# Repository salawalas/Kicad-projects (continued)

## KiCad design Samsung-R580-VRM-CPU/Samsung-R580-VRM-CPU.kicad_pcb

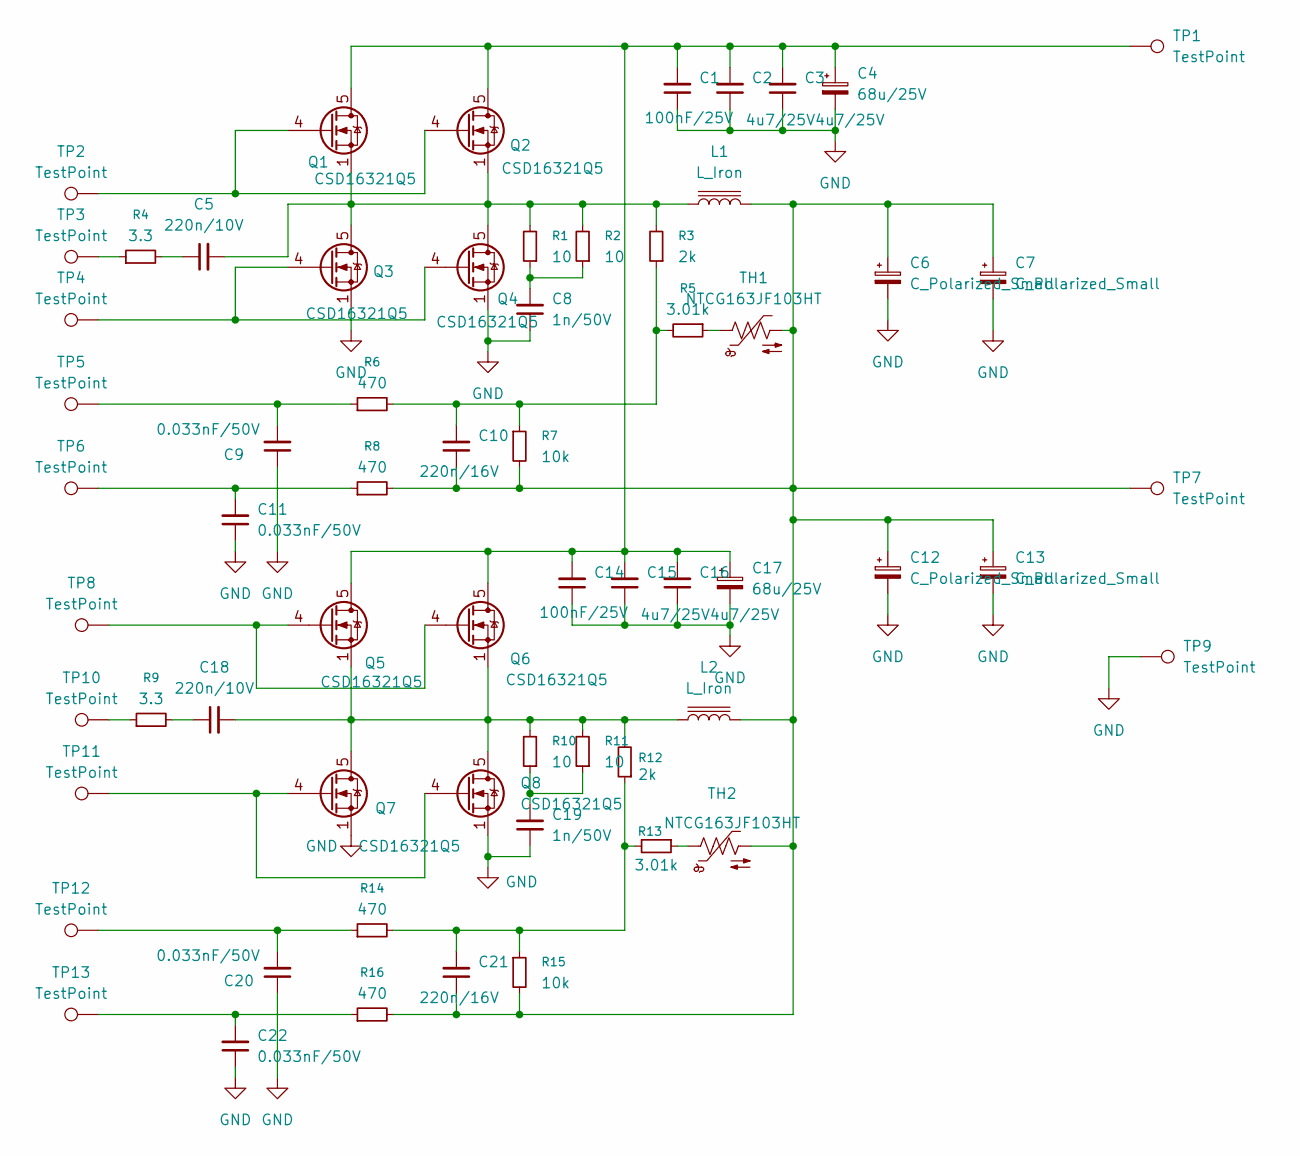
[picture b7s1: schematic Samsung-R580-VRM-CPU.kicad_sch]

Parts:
C1, C14: 100nF/25V; C_0805_2012Metric
C2, C3, C15, C16: 4u7/25V; C_0805_2012Metric
C4, C17: 68u/25V; CP_Elec_5x5.8
C5, C18: 220n/10V; C_0805_2012Metric
C6, C7, C12, C13: C_Polarized_Small; CP_EIA-3528-21_Kemet-B_HandSolder
C8, C19: 1n/50V; C_0805_2012Metric
C9, C11, C20, C22: 0.033nF/50V; C_0805_2012Metric
C10, C21: 220n/16V; C_0805_2012Metric
L1, L2: L_Iron; L_12x12mm_H6mm
Q1, Q2, Q3, Q4, Q5, Q6, Q7, Q8: CSD16321Q5; TDSON-8-1
R1, R2, R10, R11: 10; R_0805_2012Metric
R3, R12: 2k; R_0805_2012Metric
R4, R9: 3.3; R_0805_2012Metric
R5, R13: 3.01k; R_0805_2012Metric
R6, R8, R14, R16: 470; R_0805_2012Metric
R7, R15: 10k; R_0805_2012Metric
TH1, TH2: NTCG163JF103HT; R_0603_1608Metric
TP1, TP2, TP3, TP4, TP5, TP6, TP7, TP8, TP9, TP10, TP11, TP12, TP13: TestPoint; TestPoint_THTPad_1.0x1.0mm_Drill0.5mm

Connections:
GND: C1.1, C2.1, C3.1, C4.2, C6.2, C7.2, C8.1, C9.1, C11.1, C12.2, C13.2, C14.1, C15.1, C16.1, C17.2, C19.1, C20.1, C22.1, Q3.1 (S), Q3.2 (S), Q3.3 (S), Q4.1 (S), Q4.2 (S), Q4.3 (S), Q7.1 (S), Q7.2 (S), Q7.3 (S), Q8.1 (S), Q8.2 (S), Q8.3 (S), TP9.1
unnamed: C5.1, R4.2
unnamed: C8.2, R1.1, R2.1
unnamed: C9.2, R6.1, TP5.1
unnamed: C6.1, C7.1, C10.1, C12.1, C13.1, C21.1, L1.2, L2.2, R7.2, R8.2, R15.2, R16.2, TH1.2, TH2.2, TP7.1
unnamed: C10.2, R3.1, R5.2, R6.2, R7.1
unnamed: C11.2, R8.1, TP6.1
unnamed: C18.1, R9.2
unnamed: C19.2, R10.1, R11.1
unnamed: C20.2, R14.1, TP12.1
unnamed: C21.2, R12.1, R13.2, R14.2, R15.1
unnamed: C22.2, R16.1, TP13.1
unnamed: C1.2, C2.2, C3.2, C4.1, C14.2, C15.2, C16.2, C17.1, Q1.5 (D), Q2.5 (D), Q5.5 (D), Q6.5 (D), TP1.1
unnamed: Q1.4 (G), Q2.4 (G), TP2.1
unnamed: C5.2, L1.1, Q1.1 (S), Q1.2 (S), Q1.3 (S), Q2.1 (S), Q2.2 (S), Q2.3 (S), Q3.5 (D), Q4.5 (D), R1.2, R2.2, R3.2
unnamed: Q3.4 (G), Q4.4 (G), TP4.1
unnamed: Q5.4 (G), Q6.4 (G), TP8.1
unnamed: C18.2, L2.1, Q5.1 (S), Q5.2 (S), Q5.3 (S), Q6.1 (S), Q6.2 (S), Q6.3 (S), Q7.5 (D), Q8.5 (D), R10.2, R11.2, R12.2
unnamed: Q7.4 (G), Q8.4 (G), TP11.1
unnamed: R4.1, TP3.1
unnamed: R5.1, TH1.1
unnamed: R9.1, TP10.1
unnamed: R13.1, TH2.1

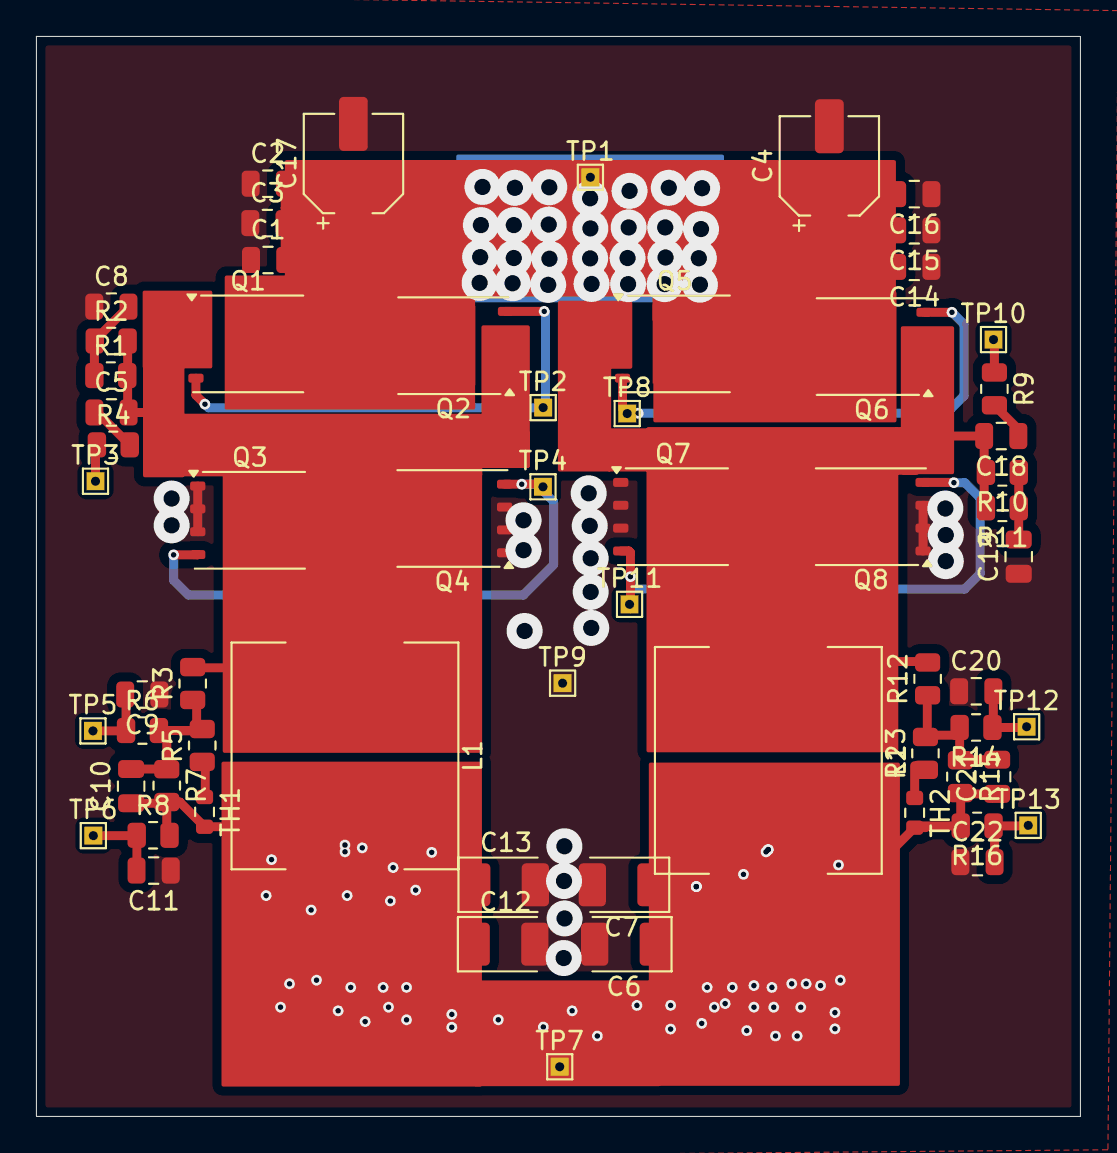
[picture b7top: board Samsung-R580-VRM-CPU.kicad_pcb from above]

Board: 6 copper layers, 58.0 x 60.0 mm, 63 parts (0 on the bottom side), 23 nets.

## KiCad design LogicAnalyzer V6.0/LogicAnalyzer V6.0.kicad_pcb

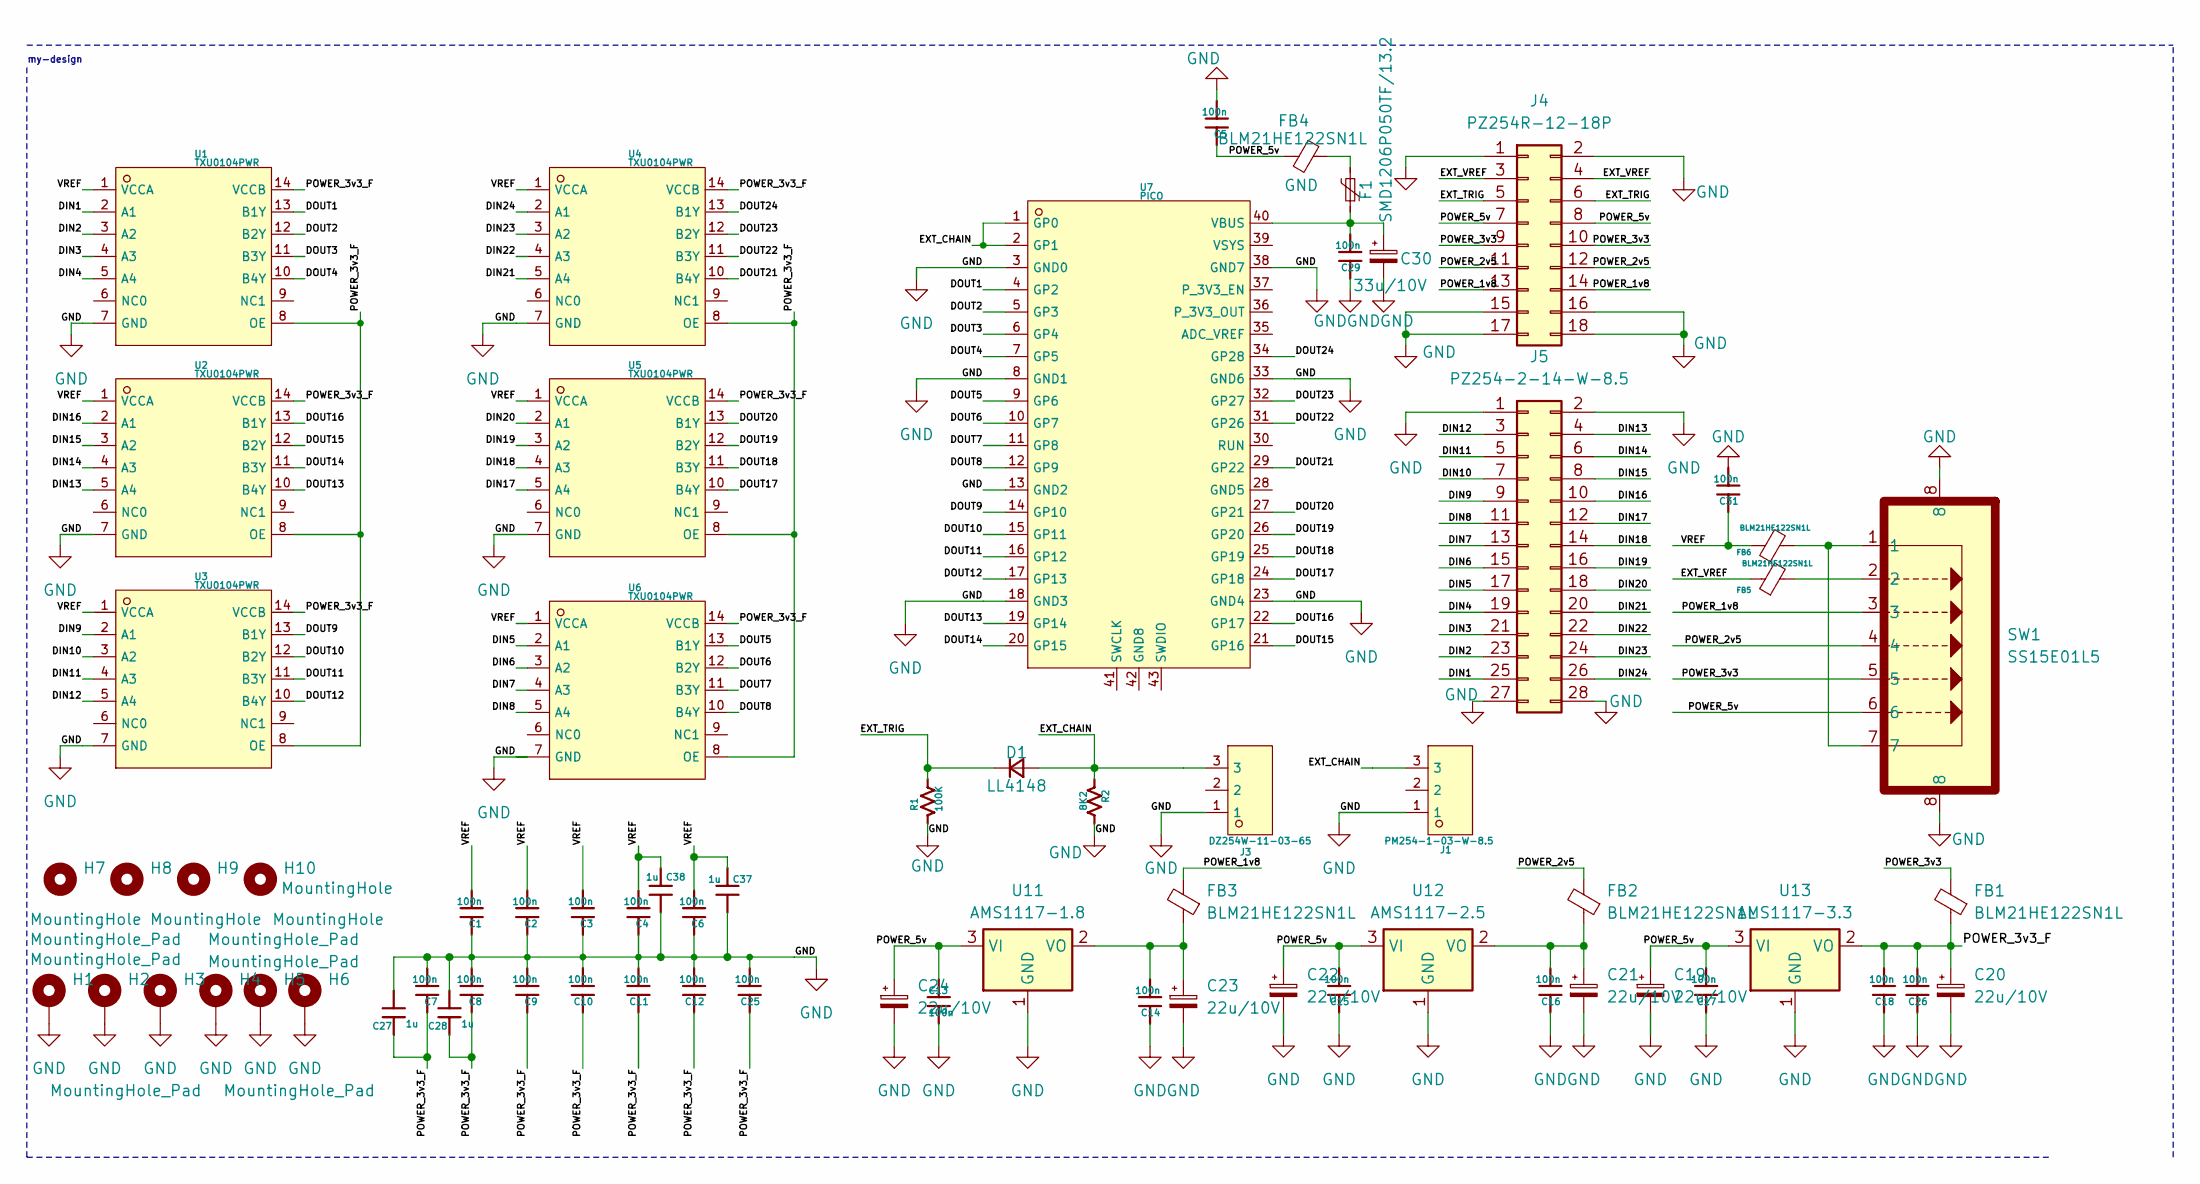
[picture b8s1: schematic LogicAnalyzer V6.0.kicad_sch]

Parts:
C1, C2, C3, C4, C5, C6, C7, C8, C9, C10, C11, C12, C13, C14, C15, C16, C17, C18, C25, C26, C29, C31: 100n; C_0805_2012Metric; MPN 0402X104M160CT
C19, C20, C21, C22, C23, C24: 22u/10V; CP_Radial_Tantal_D4.5mm_P2.50mm
C27, C28, C37, C38: 1u; C_0805_2012Metric; MPN 0402X104M160CT
C30: 33u/10V; CP_Radial_Tantal_D4.5mm_P2.50mm
D1: LL4148; D_MiniMELF
F1: SMD1206P050TF/13.2; Fuse_1206_3216Metric_Pad1.42x1.75mm_HandSolder
FB1, FB2, FB3, FB4, FB5, FB6: BLM21HE122SN1L; L_0805_2012Metric
H1, H2, H3, H4, H5, H6: MountingHole_Pad; MountingHole_2.5mm_Pad_Via
H7, H8, H9, H10: MountingHole; MountingHole_2.2mm_M2
J1: PM254-1-03-W-8.5; PinHeader_1x03_P2.54mm_Horizontal; MPN PM254-1-03-W-8.5
J3: DZ254W-11-03-65; PinHeader_1x03_P2.54mm_Horizontal; MPN DZ254W-11-03-65
J4: PZ254R-12-18P; PinHeader_2x09_P2.54mm_Horizontal
J5: PZ254-2-14-W-8.5; PinHeader_2x14_P2.54mm_Horizontal
R1: 100K; R_0805_2012Metric; MPN CRCW0402100KFKEE
R2: 8K2; R_0805_2012Metric; MPN CR0402AJW-822GLF
SW1: SS15E01L5; XKB Connection SS15E01L5
U1: TXU0104PWR; TSSOP_14_L5_0_W4_4_P0_65_LS6_4_BL_5; MPN TXU0104PWR
U2: TXU0104PWR; TSSOP_14_L5_0_W4_4_P0_65_LS6_4_BL_4; MPN TXU0104PWR
U3: TXU0104PWR; TSSOP_14_L5_0_W4_4_P0_65_LS6_4_BL; MPN TXU0104PWR
U4: TXU0104PWR; TSSOP_14_L5_0_W4_4_P0_65_LS6_4_BL_3; MPN TXU0104PWR
U5: TXU0104PWR; TSSOP_14_L5_0_W4_4_P0_65_LS6_4_BL_1; MPN TXU0104PWR
U6: TXU0104PWR; TSSOP_14_L5_0_W4_4_P0_65_LS6_4_BL_2; MPN TXU0104PWR
U7: PICO; COMM_SMD_L51_0_W21_0_P2_54_SC0916; MPN PICO
U11: AMS1117-1.8; SOT-223-3_TabPin2
U12: AMS1117-2.5; SOT-223-3_TabPin2
U13: AMS1117-3.3; SOT-223-3_TabPin2

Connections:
/DIN1: J5.25, U1.2 (A1)
/DIN2: J5.23, U1.3 (A2)
/DIN3: J5.21, U1.4 (A3)
/DIN4: J5.19, U1.5 (A4)
/DIN5: J5.17, U6.2 (A1)
/DIN6: J5.15, U6.3 (A2)
/DIN7: J5.13, U6.4 (A3)
/DIN8: J5.11, U6.5 (A4)
/DIN9: J5.9, U3.2 (A1)
/DIN10: J5.7, U3.3 (A2)
/DIN11: J5.5, U3.4 (A3)
/DIN12: J5.3, U3.5 (A4)
/DIN13: J5.4, U2.5 (A4)
/DIN14: J5.6, U2.4 (A3)
/DIN15: J5.8, U2.3 (A2)
/DIN16: J5.10, U2.2 (A1)
/DIN17: J5.12, U5.5 (A4)
/DIN18: J5.14, U5.4 (A3)
/DIN19: J5.16, U5.3 (A2)
/DIN20: J5.18, U5.2 (A1)
/DIN21: J5.20, U4.5 (A4)
/DIN22: J5.22, U4.4 (A3)
/DIN23: J5.24, U4.3 (A2)
/DIN24: J5.26, U4.2 (A1)
/DOUT1: U1.13 (B1Y), U7.4 (GP2)
/DOUT2: U1.12 (B2Y), U7.5 (GP3)
/DOUT3: U1.11 (B3Y), U7.6 (GP4)
/DOUT4: U1.10 (B4Y), U7.7 (GP5)
/DOUT5: U6.13 (B1Y), U7.9 (GP6)
/DOUT6: U6.12 (B2Y), U7.10 (GP7)
/DOUT7: U6.11 (B3Y), U7.11 (GP8)
/DOUT8: U6.10 (B4Y), U7.12 (GP9)
/DOUT9: U3.13 (B1Y), U7.14 (GP10)
/DOUT10: U3.12 (B2Y), U7.15 (GP11)
/DOUT11: U3.11 (B3Y), U7.16 (GP12)
/DOUT12: U3.10 (B4Y), U7.17 (GP13)
/DOUT13: U2.10 (B4Y), U7.19 (GP14)
/DOUT14: U2.11 (B3Y), U7.20 (GP15)
/DOUT15: U2.12 (B2Y), U7.21 (GP16)
/DOUT16: U2.13 (B1Y), U7.22 (GP17)
/DOUT17: U5.10 (B4Y), U7.24 (GP18)
/DOUT18: U5.11 (B3Y), U7.25 (GP19)
/DOUT19: U5.12 (B2Y), U7.26 (GP20)
/DOUT20: U5.13 (B1Y), U7.27 (GP21)
/DOUT21: U4.10 (B4Y), U7.29 (GP22)
/DOUT22: U4.11 (B3Y), U7.31 (GP26)
/DOUT23: U4.12 (B2Y), U7.32 (GP27)
/DOUT24: U4.13 (B1Y), U7.34 (GP28)
/EXT_CHAIN: D1.2 (A), J1.3, J3.3, R2.1, U7.1 (GP0), U7.2 (GP1)
/EXT_TRIG: D1.1 (K), J4.5, J4.6, R1.2
/EXT_VREF: FB5.1, J4.3, J4.4
/POWER_1v8: FB3.2, J4.13, J4.14, SW1.3
/POWER_2v5: FB2.2, J4.11, J4.12, SW1.4
/POWER_3v3: FB1.2, J4.9, J4.10, SW1.5
/POWER_3v3_F: C7.1, C8.1, C9.1, C10.1, C11.1, C12.1, C18.2, C20.1, C25.1, C26.2, C27.2, C28.2, FB1.1, U1.8 (OE), U1.14 (VCCB), U2.8 (OE), U2.14 (VCCB), U3.8 (OE), U3.14 (VCCB), U4.8 (OE), U4.14 (VCCB), U5.8 (OE), U5.14 (VCCB), U6.8 (OE), U6.14 (VCCB), U13.2 (VO)
/POWER_5v: C5.1, C13.1, C15.2, C17.2, C19.1, C22.1, C24.1, FB4.2, J4.7, J4.8, SW1.6, U11.3 (VI), U12.3 (VI), U13.3 (VI)
/VREF: C1.2, C2.2, C3.2, C4.2, C6.2, C31.1, C37.1, C38.1, FB6.1, U1.1 (VCCA), U2.1 (VCCA), U3.1 (VCCA), U4.1 (VCCA), U5.1 (VCCA), U6.1 (VCCA)
GND: C1.1, C2.1, C3.1, C4.1, C5.2, C6.1, C7.2, C8.2, C9.2, C10.2, C11.2, C12.2, C13.2, C14.1, C15.1, C16.1, C17.1, C18.1, C19.2, C20.2, C21.2, C22.2, C23.2, C24.2, C25.2, C26.1, C27.1, C28.1, C29.1, C30.2, C31.2, C37.2, C38.2, H1.1, H2.1, H3.1, H4.1, H5.1, H6.1, J1.1, J3.1, J4.1, J4.2, J4.15, J4.16, J4.17, J4.18, J5.1, J5.2, J5.27, J5.28, R1.1, R2.2, SW1.8, U1.7 (GND), U2.7 (GND), U3.7 (GND), U4.7 (GND), U5.7 (GND), U6.7 (GND), U7.3 (GND0), U7.8 (GND1), U7.13 (GND2), U7.18 (GND3), U7.23 (GND4), U7.33 (GND6), U7.38 (GND7), U11.1 (GND), U12.1 (GND), U13.1 (GND)
unnamed: F1.2, FB4.1
unnamed: FB5.2, SW1.2
unnamed: FB6.2, SW1.1, SW1.7
unnamed: C29.2, C30.1, F1.1, U7.40 (VBUS)
unnamed: C14.2, C23.1, FB3.1, U11.2 (VO)
unnamed: C16.2, C21.1, FB2.1, U12.2 (VO)

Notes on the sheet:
my-design

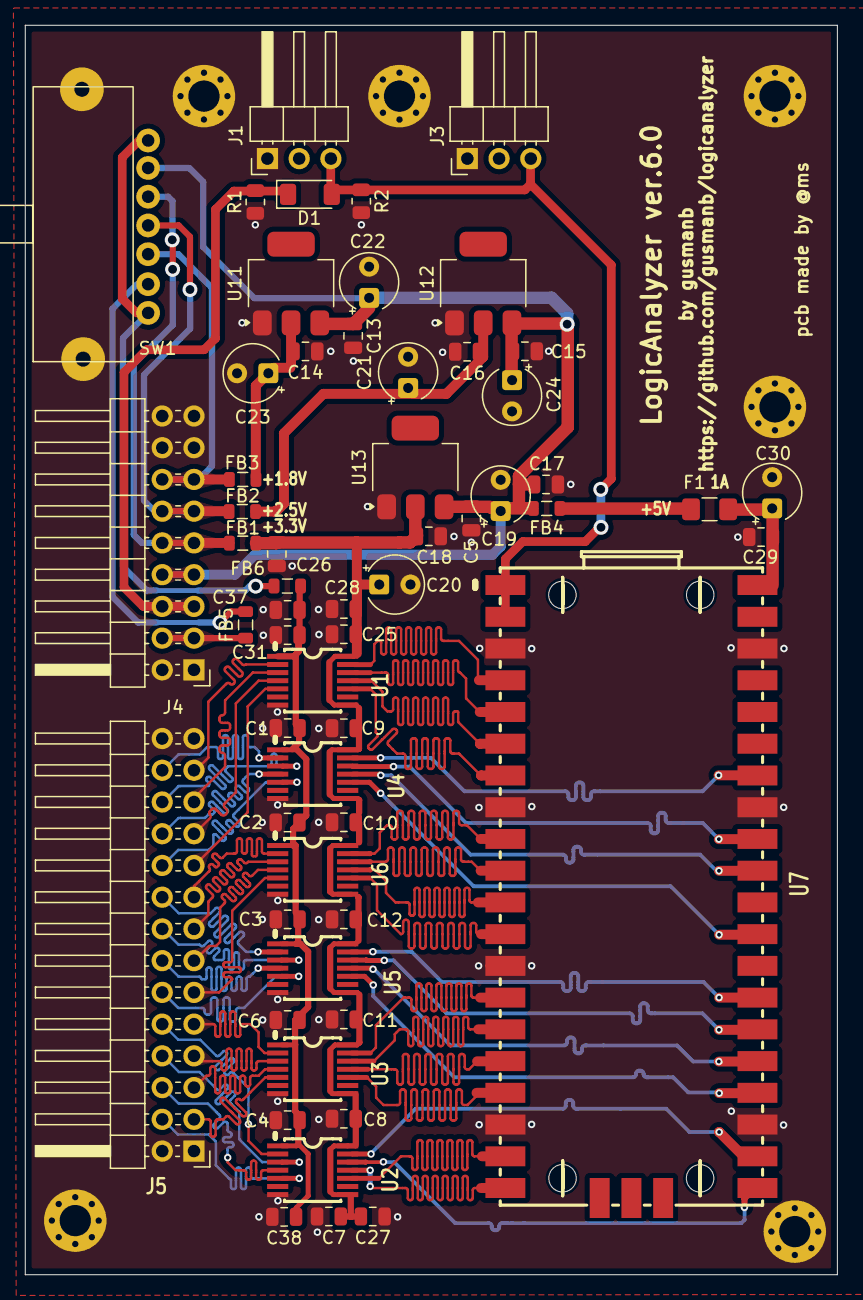
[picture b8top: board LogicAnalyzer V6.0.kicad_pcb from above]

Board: 4 copper layers, 65.0 x 100.0 mm, 68 parts (0 on the bottom side), 64 nets.

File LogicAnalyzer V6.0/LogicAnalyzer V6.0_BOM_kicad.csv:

"Reference,""Qty"",""Value"",""DNP"",""Exclude from BOM"",""Exclude from Board"",""Footprint"",""Datasheet"""
"C1,C2,C3,C4,C5,C6,C7,C8,C9,C10,C11,C12,C13,C14,C15,C16,C17,C18,C25,C26,C29,C31,""22"",""100n"","""","""","""",""Capacitor_SMD:C_0805_2012Metric"",""http://www.passivecomponent.com/wp-content/uploads/datasheet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"""
"C27,C28,C37,C38,""4"",""1u"","""","""","""",""Capacitor_SMD:C_0805_2012Metric"",""http://www.passivecomponent.com/wp-content/uploads/datasheet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"""
"F1,""1"",""1A"","""","""","""",""Fuse:Fuse_1206_3216Metric_Pad1.42x1.75mm_HandSolder"",""~"""
"J1,""1"",""PM254-1-03-W-8.5"","""","""","""",""Connector_PinHeader_2.54mm:PinHeader_1x03_P2.54mm_Horizontal"",""https://datasheet.lcsc.com/lcsc/2306091006_HCTL-PM254-1-03-W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"""
"J3,""1"",""DZ254W-11-03-65"","""","""","""",""Connector_PinHeader_2.54mm:PinHeader_1x03_P2.54mm_Horizontal"",""https://datasheet.lcsc.com/lcsc/2201121730_DEALON-DZ254W-11-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"""
"J4,""1"",""HC-PZ254-13.8L-2x9PWA"","""","""","""",""Connector_PinHeader_2.54mm:PinHeader_2x09_P2.54mm_Horizontal"",""https://www.lcsc.com/datasheet/C41376126.pdf"""
"J5,""1"",""HC-PZ254-13.8L-2x14PWA"","""","""","""",""Connector_PinHeader_2.54mm:PinHeader_2x14_P2.54mm_Horizontal"",""https://www.lcsc.com/datasheet/C42163071.pdf"""
"R1,""1"",""100K"","""","""","""",""Resistor_SMD:R_0805_2012Metric"",""https://www.vishay.com/docs/20035/dcrcwe3.pdf"""
"R2,""1"",""8K2"","""","""","""",""Resistor_SMD:R_0805_2012Metric"",""https://www.bourns.com/docs/product-datasheets/crxxxxa.pdf"""
"SW1,""1"",""SS15E01L5"","""","""","""",""Przelaczniki:XKB Connection SS15E01L5"",""https://lcsc.com/datasheet/lcsc_datasheet_2110111930_XKB-Con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"""
"U1,""1"",""TXU0104PWR"","""","""","""",""jitx-design:TSSOP_14_L5_0_W4_4_P0_65_LS6_4_BL_5"",""https://www.ti.com/cn/lit/gpn/txu0104"""
"U2,""1"",""TXU0104PWR"","""","""","""",""jitx-design:TSSOP_14_L5_0_W4_4_P0_65_LS6_4_BL_4"",""https://www.ti.com/cn/lit/gpn/txu0104"""
"U3,""1"",""TXU0104PWR"","""","""","""",""jitx-design:TSSOP_14_L5_0_W4_4_P0_65_LS6_4_BL"",""https://www.ti.com/cn/lit/gpn/txu0104"""
"U4,""1"",""TXU0104PWR"","""","""","""",""jitx-design:TSSOP_14_L5_0_W4_4_P0_65_LS6_4_BL_3"",""https://www.ti.com/cn/lit/gpn/txu0104"""
"U5,""1"",""TXU0104PWR"","""","""","""",""jitx-design:TSSOP_14_L5_0_W4_4_P0_65_LS6_4_BL_1"",""https://www.ti.com/cn/lit/gpn/txu0104"""
"U6,""1"",""TXU0104PWR"","""","""","""",""jitx-design:TSSOP_14_L5_0_W4_4_P0_65_LS6_4_BL_2"",""https://www.ti.com/cn/lit/gpn/txu0104"""
